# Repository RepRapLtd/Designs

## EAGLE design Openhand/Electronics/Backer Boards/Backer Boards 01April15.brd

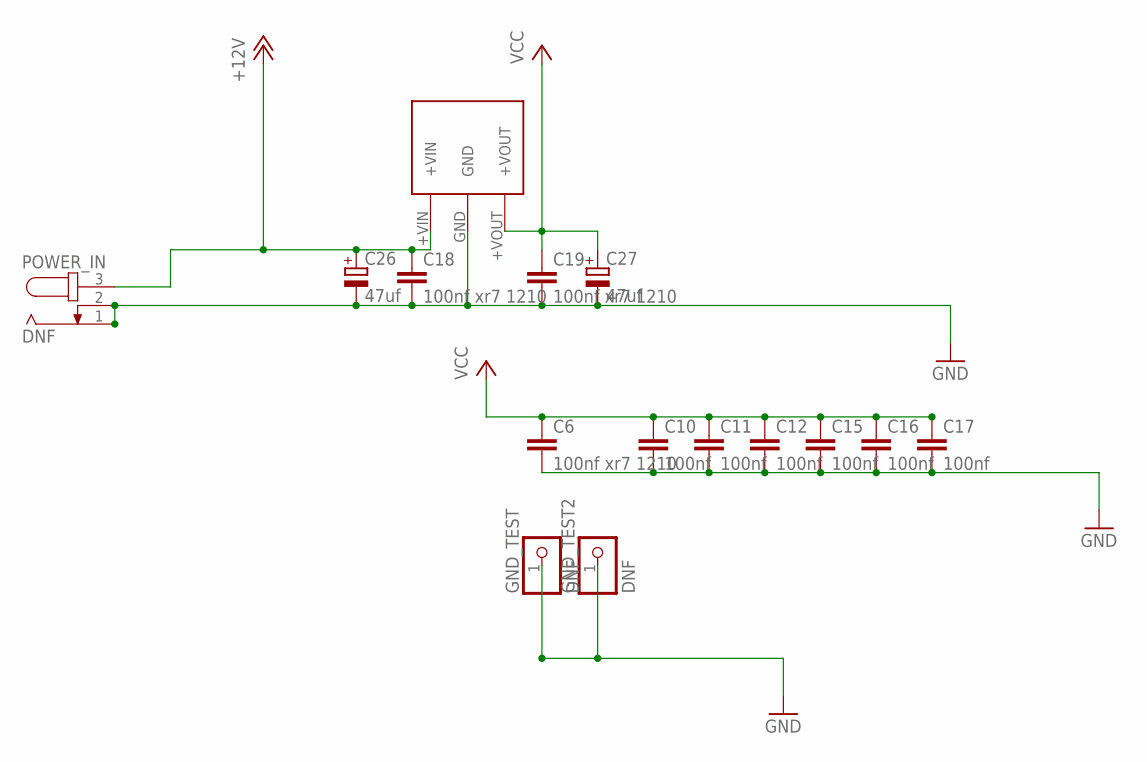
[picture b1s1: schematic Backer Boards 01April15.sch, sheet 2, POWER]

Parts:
5V_REG: DNF; 5V_RECOM_0.5A_REGULATOR
C6, C18, C19: 100nf xr7 1210; C1210
C10, C11, C12, C15, C16, C17: 100nf; C0603
C26, C27: 47uf; PANASONIC_C
GND_TEST, GND_TEST2: DNF; 1X01_ROUND
POWER_IN: DNF; SPC4078

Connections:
+12V: 5V_REG.+VIN, C18.1, C26.+, POWER_IN.3; also elsewhere on the board
GND: 5V_REG.GND, C6.2, C10.2, C11.2, C12.2, C15.2, C16.2, C17.2, C18.2, C19.2, C26.-, C27.-, GND_TEST.1, GND_TEST2.1, POWER_IN.1, POWER_IN.2; also elsewhere on the board
VCC: 5V_REG.+VOUT, C6.1, C10.1, C11.1, C12.1, C15.1, C16.1, C17.1, C19.1, C27.+; also elsewhere on the board

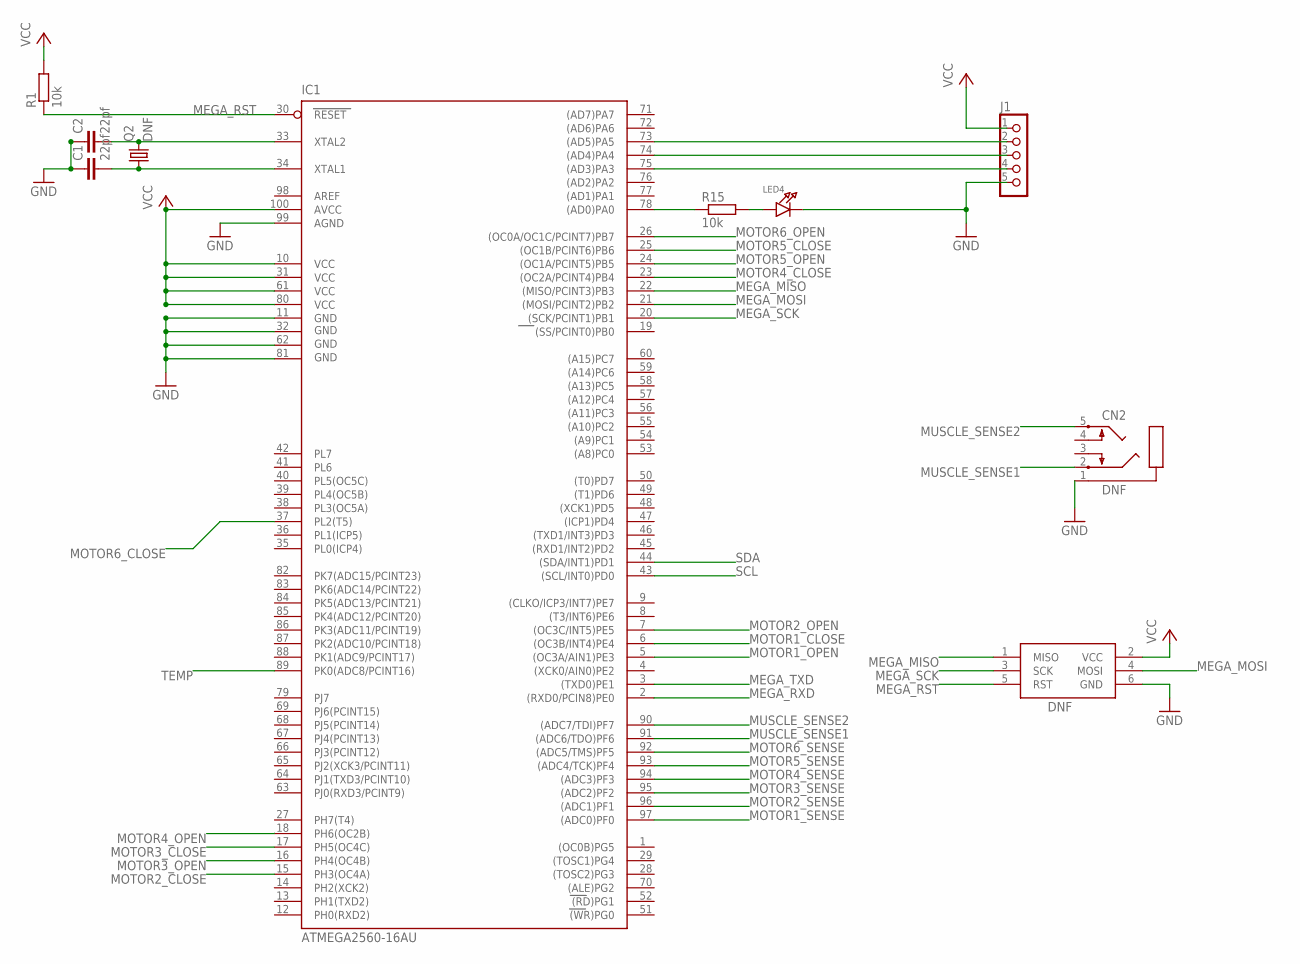
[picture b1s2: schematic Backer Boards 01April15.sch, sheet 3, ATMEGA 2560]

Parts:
C1, C2: 22pf; C0603
CN2: DNF; STX3100
DNF: AVRISP-6; AVRISP
IC1: ATMEGA2560-16AU; TQFP100
J1: DNF; M1X5
LED4: LED0805; CHIPLED_0805
Q2: DNF; HC49/S
R1, R15: 10k; R0603

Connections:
GND: C1.1, C2.1, CN2.1, DNF.6 (GND), IC1.11 (GND), IC1.32 (GND1), IC1.62 (GND2), IC1.81 (GND3), IC1.99 (AGND), J1.5, LED4.C; also elsewhere on the board
MEGA_MISO: DNF.1 (MISO), IC1.22 ((MISO/PCINT3)PB3)
MEGA_MOSI: DNF.4 (MOSI), IC1.21 ((MOSI/PCINT2)PB2)
MEGA_RST: DNF.5 (RST), IC1.30 (RESET), R1.1; also elsewhere on the board
MEGA_RXD: IC1.2 ((RXD0/PCIN8)PE0); also elsewhere on the board
MEGA_SCK: DNF.3 (SCK), IC1.20 ((SCK/PCINT1)PB1)
MEGA_TXD: IC1.3 ((TXD0)PE1); also elsewhere on the board
MOTOR1_CLOSE: IC1.6 ((OC3B/INT4)PE4); also elsewhere on the board
MOTOR1_OPEN: IC1.5 ((OC3A/AIN1)PE3); also elsewhere on the board
MOTOR1_SENSE: IC1.97 ((ADC0)PF0); also elsewhere on the board
MOTOR2_CLOSE: IC1.15 (PH3(OC4A)); also elsewhere on the board
MOTOR2_OPEN: IC1.7 ((OC3C/INT5)PE5); also elsewhere on the board
MOTOR2_SENSE: IC1.96 ((ADC1)PF1); also elsewhere on the board
MOTOR3_CLOSE: IC1.17 (PH5(OC4C)); also elsewhere on the board
MOTOR3_OPEN: IC1.16 (PH4(OC4B)); also elsewhere on the board
MOTOR3_SENSE: IC1.95 ((ADC2)PF2); also elsewhere on the board
MOTOR4_CLOSE: IC1.23 ((OC2A/PCINT4)PB4); also elsewhere on the board
MOTOR4_OPEN: IC1.18 (PH6(OC2B)); also elsewhere on the board
MOTOR4_SENSE: IC1.94 ((ADC3)PF3); also elsewhere on the board
MOTOR5_CLOSE: IC1.25 ((OC1B/PCINT6)PB6); also elsewhere on the board
MOTOR5_OPEN: IC1.24 ((OC1A/PCINT5)PB5); also elsewhere on the board
MOTOR5_SENSE: IC1.93 ((ADC4/TCK)PF4); also elsewhere on the board
MOTOR6_CLOSE: IC1.37 (PL2(T5))
MOTOR6_OPEN: IC1.26 ((OC0A/OC1C/PCINT7)PB7)
MOTOR6_SENSE: IC1.92 ((ADC5/TMS)PF5)
MUSCLE_SENSE1: CN2.2, IC1.91 ((ADC6/TDO)PF6)
MUSCLE_SENSE2: CN2.5, IC1.90 ((ADC7/TDI)PF7)
unnamed: IC1.78 ((AD0)PA0), R15.1
unnamed: LED4.A, R15.2
unnamed: IC1.75 ((AD3)PA3), J1.4
unnamed: IC1.74 ((AD4)PA4), J1.3
unnamed: IC1.73 ((AD5)PA5), J1.2
SCL: IC1.43 ((SCL/INT0)PD0)
SDA: IC1.44 ((SDA/INT1)PD1)
TEMP: IC1.89 (PK0(ADC8/PCINT16))
VCC: DNF.2 (VCC), IC1.10 (VCC), IC1.31 (VCC1), IC1.61 (VCC2), IC1.80 (VCC3), IC1.100 (AVCC), J1.1, R1.2; also elsewhere on the board
XTAL1: C1.2, IC1.34 (XTAL1), Q2.1
XTAL2: C2.2, IC1.33 (XTAL2), Q2.2

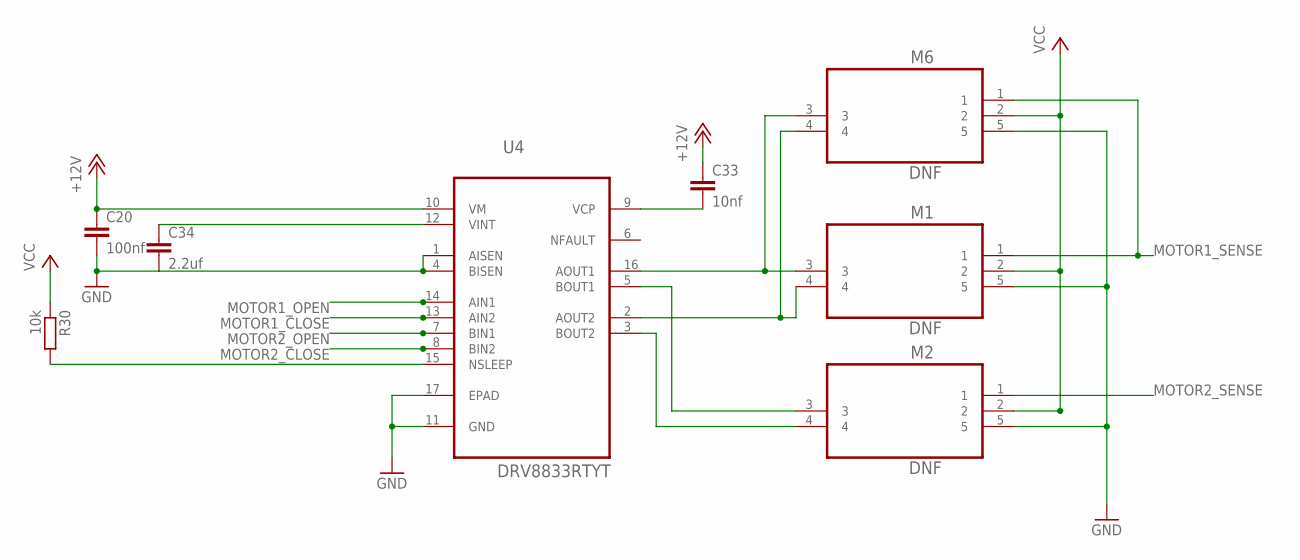
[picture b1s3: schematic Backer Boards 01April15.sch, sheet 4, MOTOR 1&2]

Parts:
C20: 100nf; C0603
C33: 10nf; C0603
C34: 2.2uf; C0603
M1, M2, M6: DNF; FCI_SFW5R-1STE1LF
R30: 10k; R0603
U4: DRV8833RTYT; QFN65P400X400X80-17N

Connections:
+12V: C20.1, C33.1, U4.10 (VM); also elsewhere on the board
GND: C20.2, C34.2, M1.5, M2.5, M6.5, U4.1 (AISEN), U4.4 (BISEN), U4.11 (GND), U4.17 (EPAD); also elsewhere on the board
MOTOR1_CLOSE: U4.13 (AIN2); also elsewhere on the board
MOTOR1_OPEN: U4.14 (AIN1); also elsewhere on the board
MOTOR1_SENSE: M1.1, M6.1; also elsewhere on the board
MOTOR2_CLOSE: U4.8 (BIN2); also elsewhere on the board
MOTOR2_OPEN: U4.7 (BIN1); also elsewhere on the board
MOTOR2_SENSE: M2.1; also elsewhere on the board
unnamed: C33.2, U4.9 (VCP)
unnamed: M1.3, M6.3, U4.16 (AOUT1)
unnamed: M1.4, M6.4, U4.2 (AOUT2)
unnamed: M2.3, U4.5 (BOUT1)
unnamed: M2.4, U4.3 (BOUT2)
unnamed: R30.2, U4.15 (NSLEEP)
unnamed: C34.1, U4.12 (VINT)
VCC: M1.2, M2.2, M6.2, R30.1; also elsewhere on the board

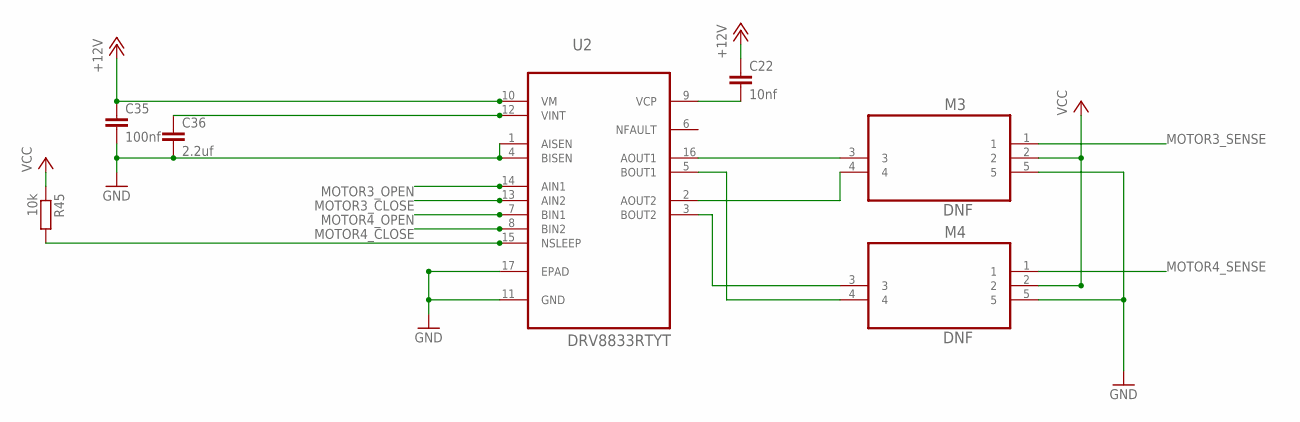
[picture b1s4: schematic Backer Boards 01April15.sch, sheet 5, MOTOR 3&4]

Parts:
C22: 10nf; C0603
C35: 100nf; C0603
C36: 2.2uf; C0603
M3, M4: DNF; FCI_SFW5R-1STE1LF
R45: 10k; R0603
U2: DRV8833RTYT; QFN65P400X400X80-17N

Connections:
+12V: C22.1, C35.1, U2.10 (VM); also elsewhere on the board
GND: C35.2, C36.2, M3.5, M4.5, U2.1 (AISEN), U2.4 (BISEN), U2.11 (GND), U2.17 (EPAD); also elsewhere on the board
MOTOR3_CLOSE: U2.13 (AIN2); also elsewhere on the board
MOTOR3_OPEN: U2.14 (AIN1); also elsewhere on the board
MOTOR3_SENSE: M3.1; also elsewhere on the board
MOTOR4_CLOSE: U2.8 (BIN2); also elsewhere on the board
MOTOR4_OPEN: U2.7 (BIN1); also elsewhere on the board
MOTOR4_SENSE: M4.1; also elsewhere on the board
unnamed: M3.3, U2.16 (AOUT1)
unnamed: M3.4, U2.2 (AOUT2)
unnamed: M4.4, U2.5 (BOUT1)
unnamed: M4.3, U2.3 (BOUT2)
unnamed: C22.2, U2.9 (VCP)
unnamed: C36.1, U2.12 (VINT)
unnamed: R45.2, U2.15 (NSLEEP)
VCC: M3.2, M4.2, R45.1; also elsewhere on the board

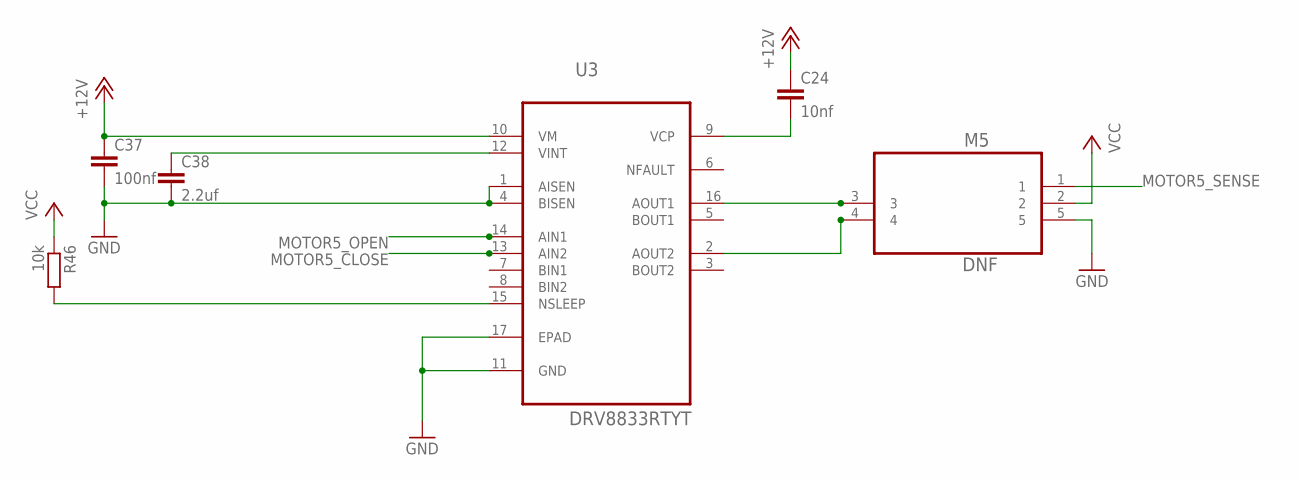
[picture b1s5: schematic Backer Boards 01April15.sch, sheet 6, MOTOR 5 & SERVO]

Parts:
C24: 10nf; C0603
C37: 100nf; C0603
C38: 2.2uf; C0603
M5: DNF; FCI_SFW5R-1STE1LF
R46: 10k; R0603
U3: DRV8833RTYT; QFN65P400X400X80-17N

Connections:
+12V: C24.1, C37.1, U3.10 (VM); also elsewhere on the board
GND: C37.2, C38.2, M5.5, U3.1 (AISEN), U3.4 (BISEN), U3.11 (GND), U3.17 (EPAD); also elsewhere on the board
MOTOR5_CLOSE: U3.13 (AIN2); also elsewhere on the board
MOTOR5_OPEN: U3.14 (AIN1); also elsewhere on the board
MOTOR5_SENSE: M5.1; also elsewhere on the board
unnamed: M5.4, U3.2 (AOUT2)
unnamed: M5.3, U3.16 (AOUT1)
unnamed: C38.1, U3.12 (VINT)
unnamed: C24.2, U3.9 (VCP)
unnamed: R46.2, U3.15 (NSLEEP)
VCC: M5.2, R46.1; also elsewhere on the board

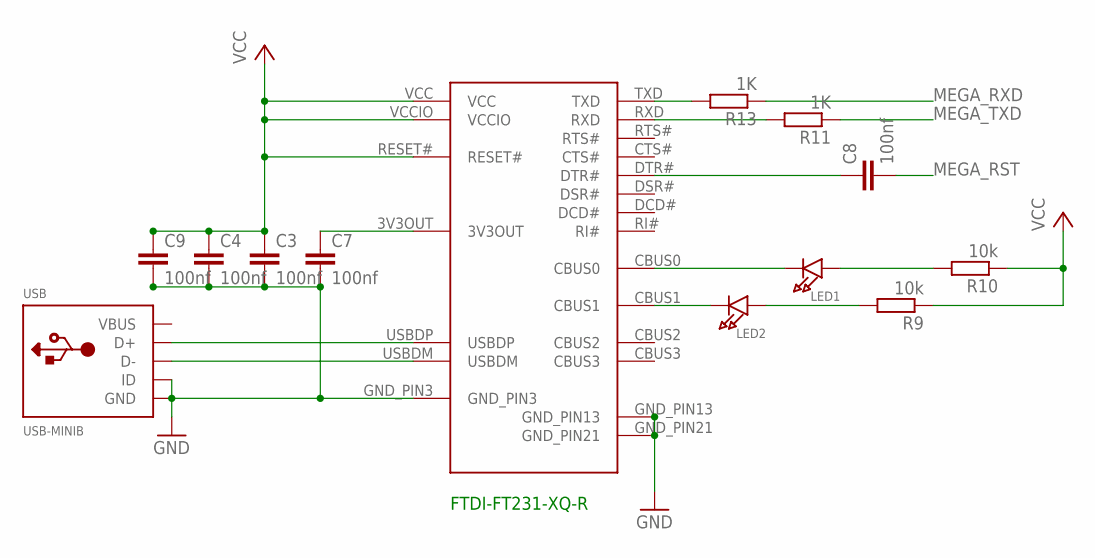
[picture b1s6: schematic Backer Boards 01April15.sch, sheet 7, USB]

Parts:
C3, C4, C7, C8, C9: 100nf; C0603
FTDI-FT231-XQ-R: FT231XQ-R; FTDI_FT231XQ-R_PACKAGE
LED1, LED2: LED0805; CHIPLED_0805
R9, R10: 10k; R0603
R11, R13: 1K; R0603
USB: USB-MINIB

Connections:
GND: C3.2, C4.2, C7.2, C9.2, FTDI-FT231-XQ-R.GND_PIN3, FTDI-FT231-XQ-R.GND_PIN13, FTDI-FT231-XQ-R.GND_PIN21, USB.GND, USB.ID; also elsewhere on the board
MEGA_RST: C8.2; also elsewhere on the board
MEGA_RXD: R13.1; also elsewhere on the board
MEGA_TXD: R11.1; also elsewhere on the board
unnamed: FTDI-FT231-XQ-R.USBDP, USB.D+
unnamed: FTDI-FT231-XQ-R.USBDM, USB.D-
unnamed: C7.1, FTDI-FT231-XQ-R.3V3OUT
unnamed: C8.1, FTDI-FT231-XQ-R.DTR#
unnamed: FTDI-FT231-XQ-R.TXD, R13.2
unnamed: FTDI-FT231-XQ-R.RXD, R11.2
unnamed: FTDI-FT231-XQ-R.CBUS0, LED1.C
unnamed: FTDI-FT231-XQ-R.CBUS1, LED2.C
unnamed: LED2.A, R9.2
unnamed: LED1.A, R10.2
VBUS: USB.VBUS
VCC: C3.1, C4.1, C9.1, FTDI-FT231-XQ-R.RESET#, FTDI-FT231-XQ-R.VCC, FTDI-FT231-XQ-R.VCCIO, R9.1, R10.1; also elsewhere on the board

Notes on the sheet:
FTDI-FT231-XQ-R

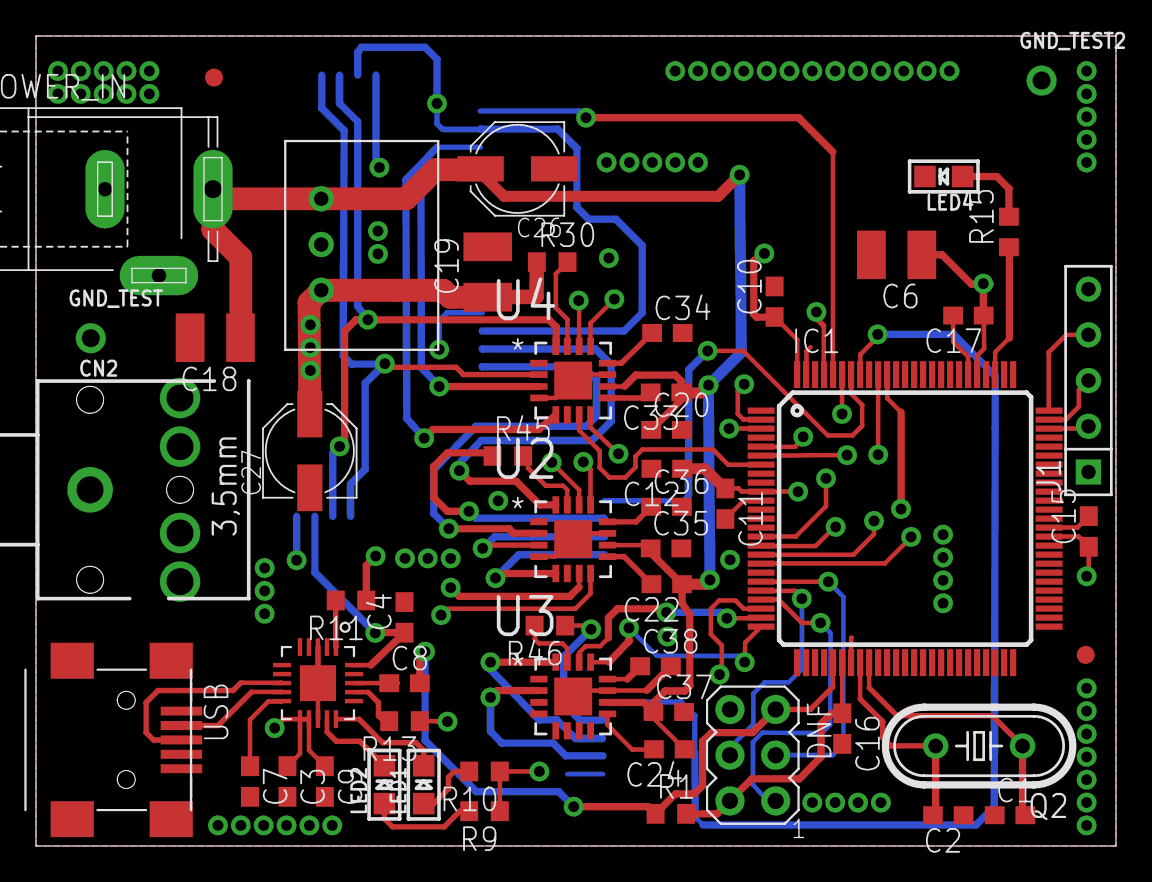
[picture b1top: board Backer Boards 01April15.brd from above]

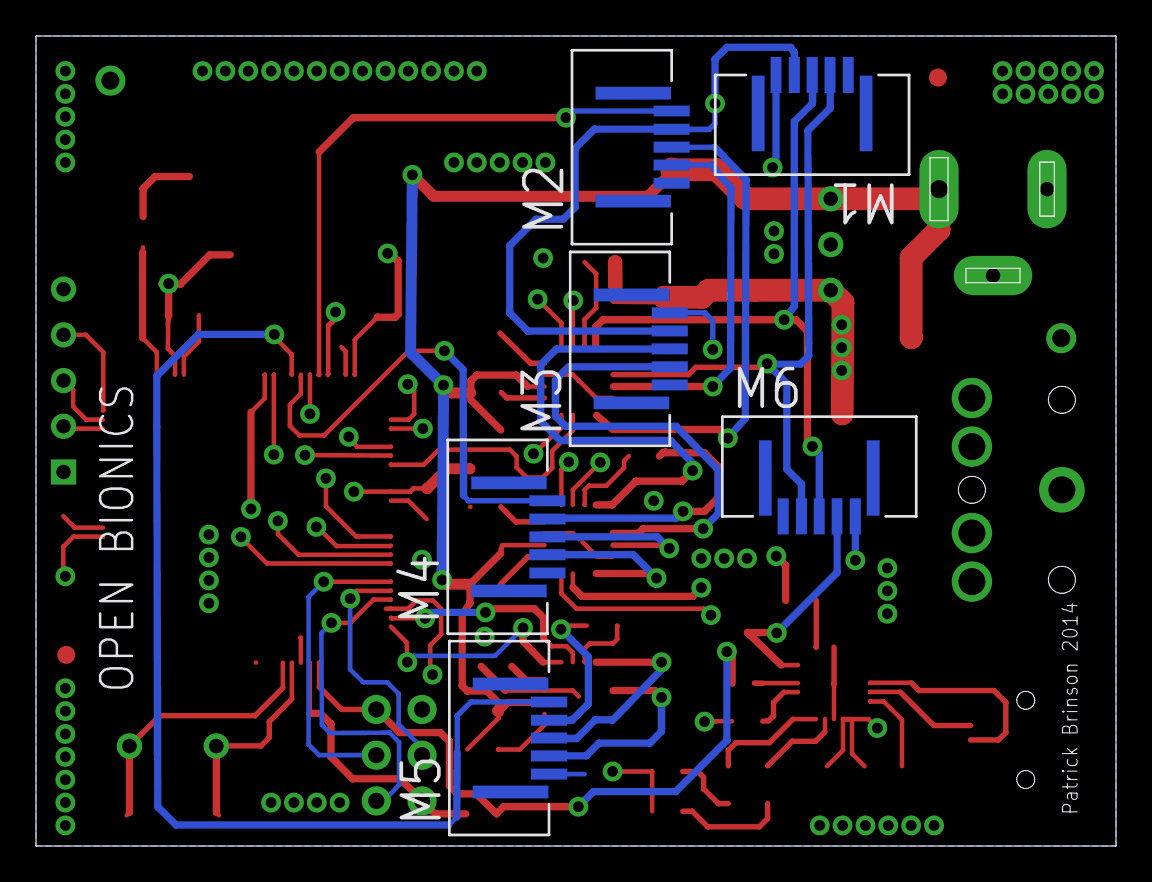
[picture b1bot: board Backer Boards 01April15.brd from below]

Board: 4 copper layers, 60.0 x 45.0 mm, 61 parts (6 on the bottom side), 62 nets.

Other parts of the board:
U$1, U$2: FIDUCIAL_G10

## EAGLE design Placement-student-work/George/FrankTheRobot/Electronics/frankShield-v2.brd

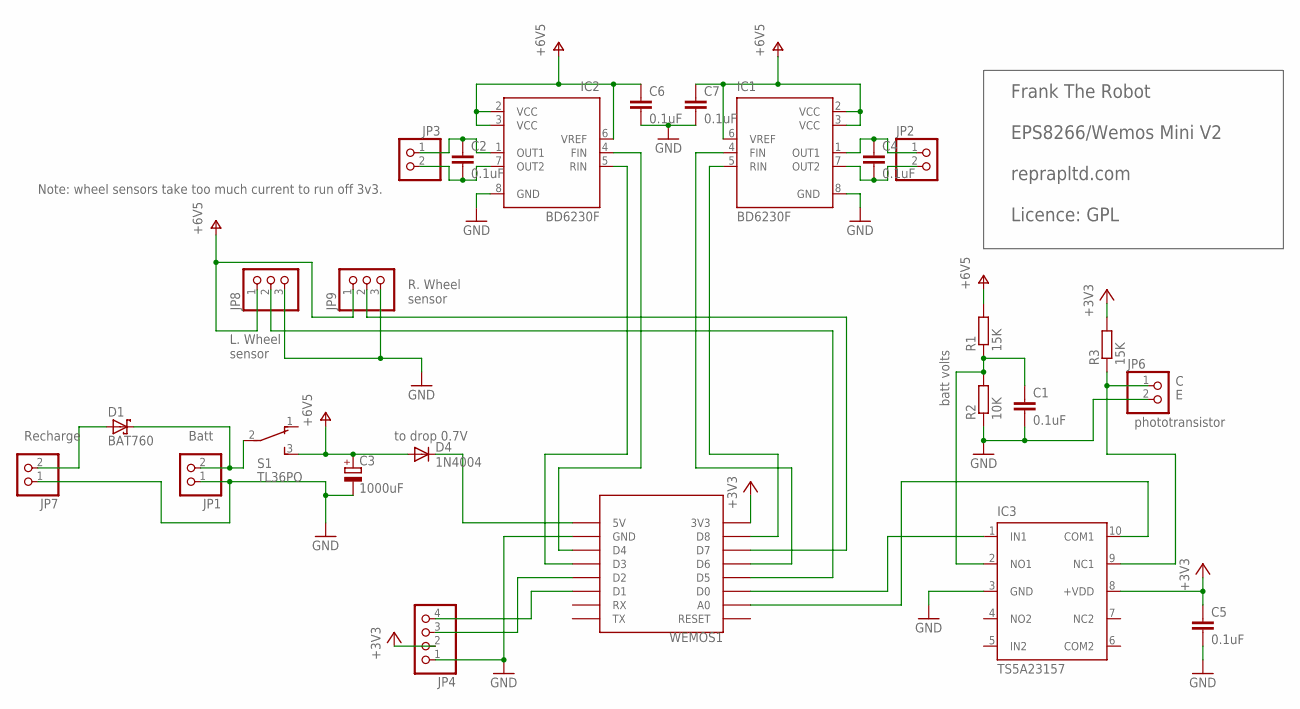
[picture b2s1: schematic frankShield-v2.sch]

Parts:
C1, C2, C4, C5, C6, C7: 0.1uF; C0805
C3: 1000uF; B45181B
D1: BAT760; SOD323_ST
D4: 1N4004; DO41-10
IC1, IC2: BD6230F; SOP8
IC3: TS5A23157; MSOP10
JP1, JP2, JP3, JP6, JP7: PINHD-1X2; 1X02
JP4: PINHD-1X4; 1X04
JP8, JP9: PINHD-1X3; 1X03
R1, R3: 15K; M0805
R2: 10K; M0805
S1: TL36PO; TL3XPO
WEMOS1: WEMOS-D1-MINI

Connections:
+3V3: C5.1, IC3.8 (+VDD), JP4.2, R3.2, WEMOS1.3V3
GND: C1.2, C3.-, C5.2, C6.2, C7.2, IC1.8 (GND), IC2.8 (GND), IC3.3 (GND), JP1.1, JP4.1, JP6.2, JP7.1, JP8.3, JP9.3, R2.1, WEMOS1.GND
unnamed: JP4.4, WEMOS1.D1
unnamed: JP4.3, WEMOS1.D2
unnamed: C2.1, IC2.1 (OUT1), JP3.1
unnamed: C2.2, IC2.7 (OUT2), JP3.2
unnamed: C4.1, IC1.1 (OUT1), JP2.1
unnamed: C4.2, IC1.7 (OUT2), JP2.2
unnamed: IC2.4 (FIN), WEMOS1.D4
unnamed: IC2.5 (RIN), WEMOS1.D3
unnamed: IC1.4 (FIN), WEMOS1.D6
unnamed: IC1.5 (RIN), WEMOS1.D8
unnamed: IC3.10 (COM1), WEMOS1.A0
unnamed: C1.1, IC3.2 (NO1), R1.1, R2.2
unnamed: D1.C, JP1.2, S1.2
unnamed: IC3.9 (NC1), JP6.1, R3.1
unnamed: IC3.1 (IN1), WEMOS1.D0
unnamed: D1.A, JP7.2
unnamed: JP9.2, WEMOS1.D7
unnamed: JP8.2, WEMOS1.D5
unnamed: D4.C, WEMOS1.5V
NC2: IC3.7 (NC2)
V+: C3.+, C6.1, C7.1, D4.A, IC1.2 (VCC), IC1.3 (VCC), IC1.6 (VREF), IC2.2 (VCC), IC2.3 (VCC), IC2.6 (VREF), JP8.1, JP9.1, R1.2, S1.3 (S)

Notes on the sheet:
phototransistor
Frank The Robot EPS8266/Wemos Mini V2 reprapltd.com Licence: GPL
Batt
Recharge
L. Wheel sensor
R. Wheel sensor
batt volts
Note: wheel sensors take too much current to run off 3v3.
to drop 0.7V

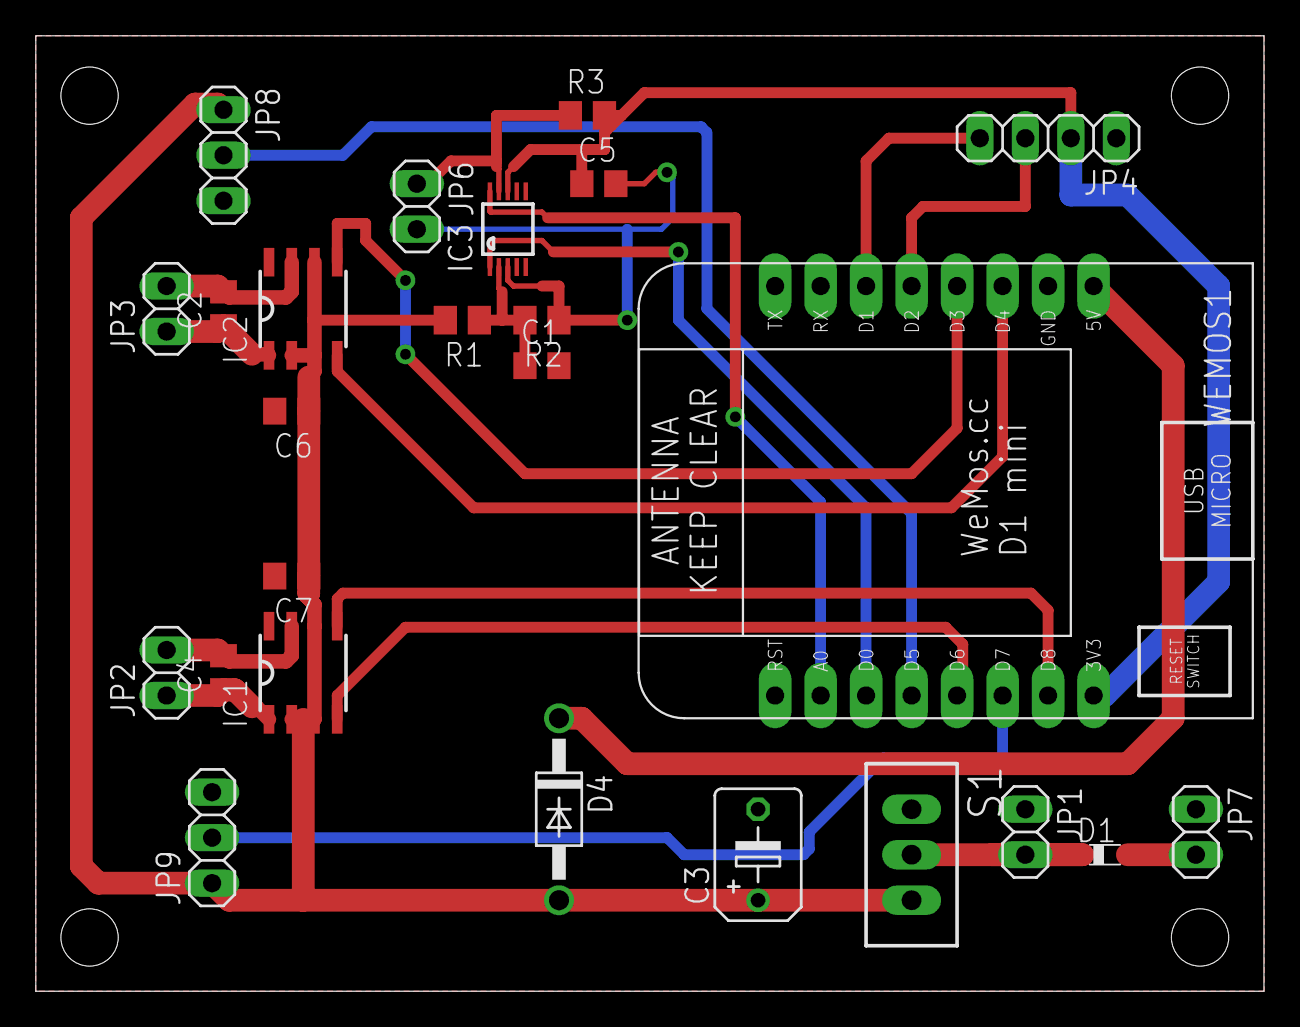
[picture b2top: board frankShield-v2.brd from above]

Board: 2 copper layers, 68.6 x 53.3 mm, 25 parts (0 on the bottom side), 22 nets.

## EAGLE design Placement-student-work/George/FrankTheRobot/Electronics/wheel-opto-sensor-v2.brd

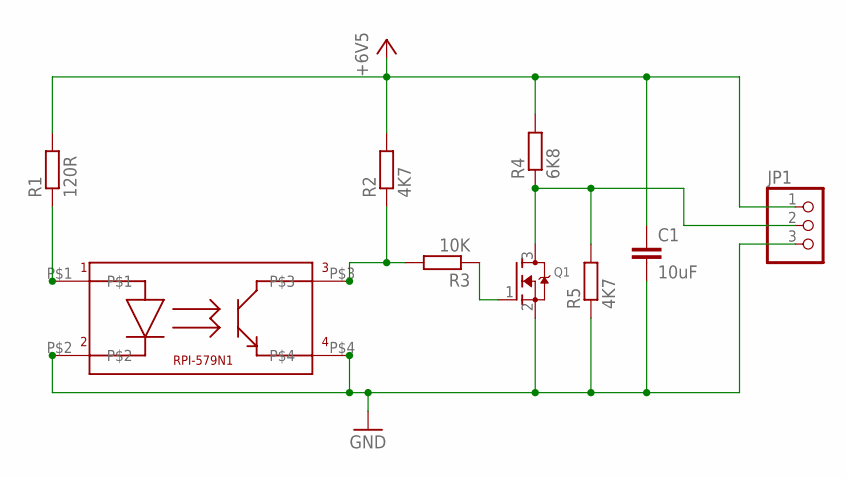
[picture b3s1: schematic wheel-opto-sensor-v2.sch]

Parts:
C1: 10uF; C1206
JP1: PINHD-1X3; 1X03
Q1: MOSFET-NREFLOW; SOT23
R1: 120R; M0805
R2, R5: 4K7; M0805
R3: 10K; M0805
R4: 6K8; M0805
U$1: RPI-579N1

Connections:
+6V5: C1.1, JP1.1, R1.2, R2.2, R4.2
GND: C1.2, JP1.3, Q1.2 (S), R5.1, U$1.P$2, U$1.P$4
unnamed: JP1.2, Q1.3 (D), R4.1, R5.2
unnamed: R1.1, U$1.P$1
unnamed: Q1.1 (G), R3.1
unnamed: R2.1, R3.2, U$1.P$3

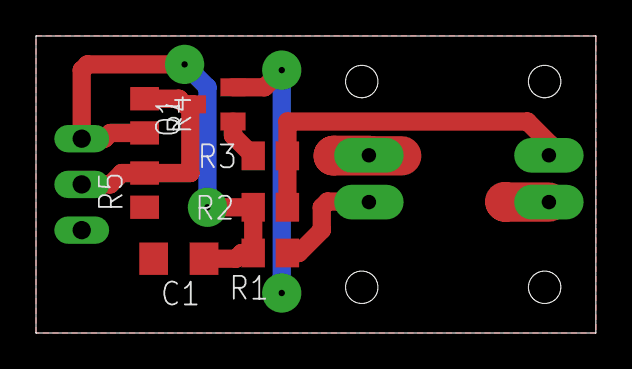
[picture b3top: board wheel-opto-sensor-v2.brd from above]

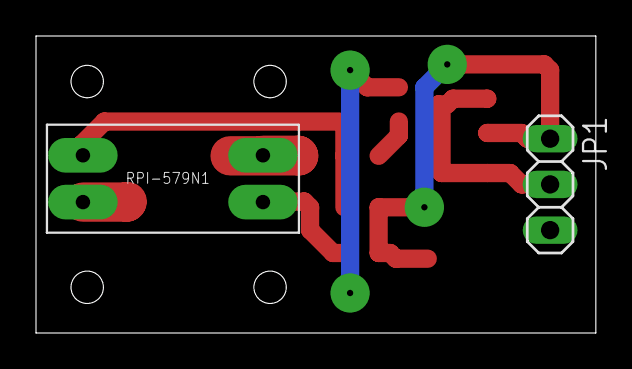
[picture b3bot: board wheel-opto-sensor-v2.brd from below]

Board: 2 copper layers, 31.1 x 16.5 mm, 9 parts (2 on the bottom side), 6 nets.

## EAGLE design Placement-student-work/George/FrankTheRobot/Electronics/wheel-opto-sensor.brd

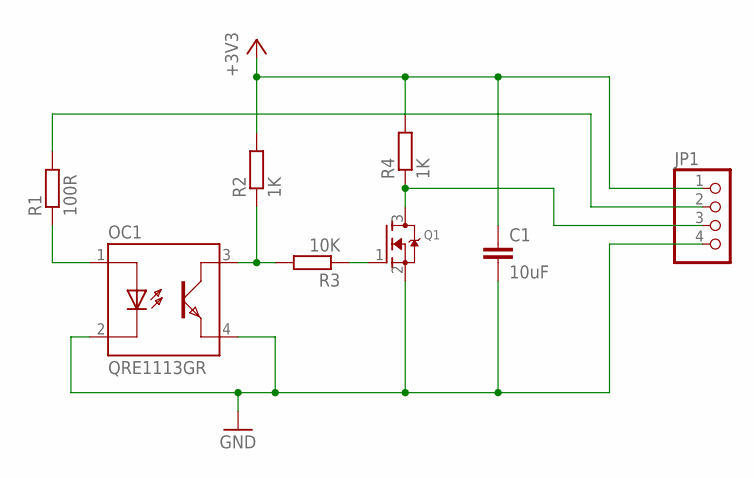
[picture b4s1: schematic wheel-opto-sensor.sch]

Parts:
C1: 10uF; C1206
JP1: PINHD-1X4; 1X04
OC1: QRE1113GR; SMT_GULLWING_4
Q1: MOSFET-NREFLOW; SOT23
R1: 100R; M0805
R2, R4: 1K; M0805
R3: 10K; M0805

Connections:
+3V3: C1.1, JP1.1, R2.2, R4.2
GND: C1.2, JP1.4, OC1.2 (C), OC1.4 (TE), Q1.2 (S)
unnamed: JP1.3, Q1.3 (D), R4.1
unnamed: OC1.1 (A), R1.1
unnamed: JP1.2, R1.2
unnamed: Q1.1 (G), R3.1
unnamed: OC1.3 (TC), R2.1, R3.2

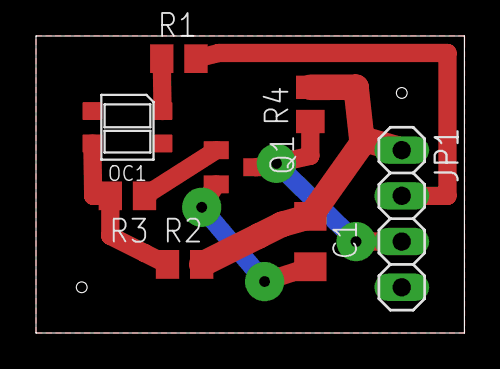
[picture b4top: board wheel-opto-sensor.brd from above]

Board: 2 copper layers, 23.8 x 16.5 mm, 8 parts (0 on the bottom side), 7 nets.

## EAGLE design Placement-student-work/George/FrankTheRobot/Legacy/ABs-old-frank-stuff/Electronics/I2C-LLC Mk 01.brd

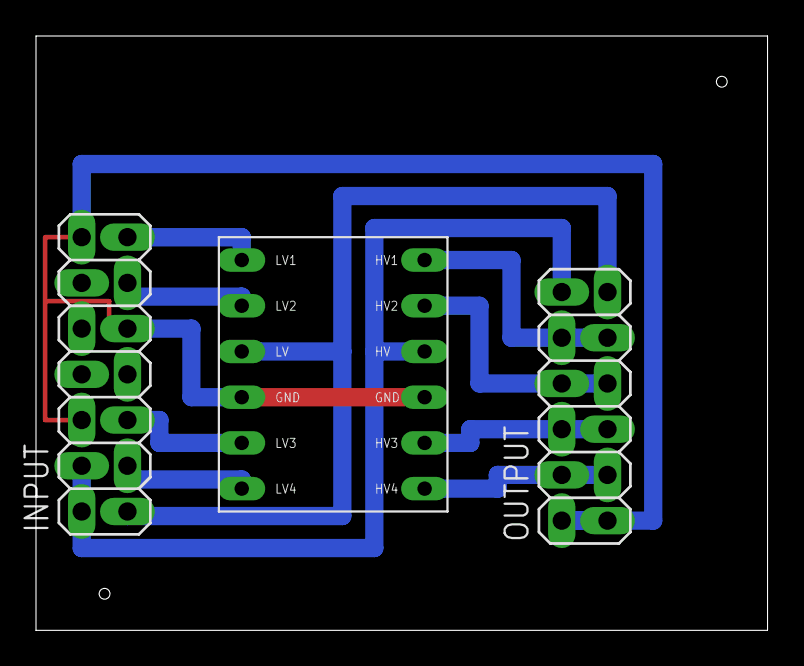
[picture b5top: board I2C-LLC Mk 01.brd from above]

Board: 2 copper layers, 40.6 x 33.0 mm, 3 parts (0 on the bottom side), 11 nets.

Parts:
INPUT: 2X07
OUTPUT: 2X06
U$1: BD-LLC

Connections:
+3V3: INPUT.1, OUTPUT.11, U$1.LV_IN
+5V: INPUT.2, INPUT.4, OUTPUT.12, U$1.HV_IN
EX1_H: OUTPUT.7, OUTPUT.8, U$1.HV2
EX1_L: INPUT.11, U$1.LV2
EX2_H: OUTPUT.9, OUTPUT.10, U$1.HV1
EX2_L: INPUT.13, U$1.LV1
GND: INPUT.6, INPUT.9, INPUT.14, OUTPUT.1, OUTPUT.2, U$1.GND1, U$1.GND2
SCK_H: OUTPUT.5, OUTPUT.6, U$1.HV3
SCK_L: INPUT.5, U$1.LV3
SDA_H: OUTPUT.3, OUTPUT.4, U$1.HV4
SDA_L: INPUT.3, U$1.LV4

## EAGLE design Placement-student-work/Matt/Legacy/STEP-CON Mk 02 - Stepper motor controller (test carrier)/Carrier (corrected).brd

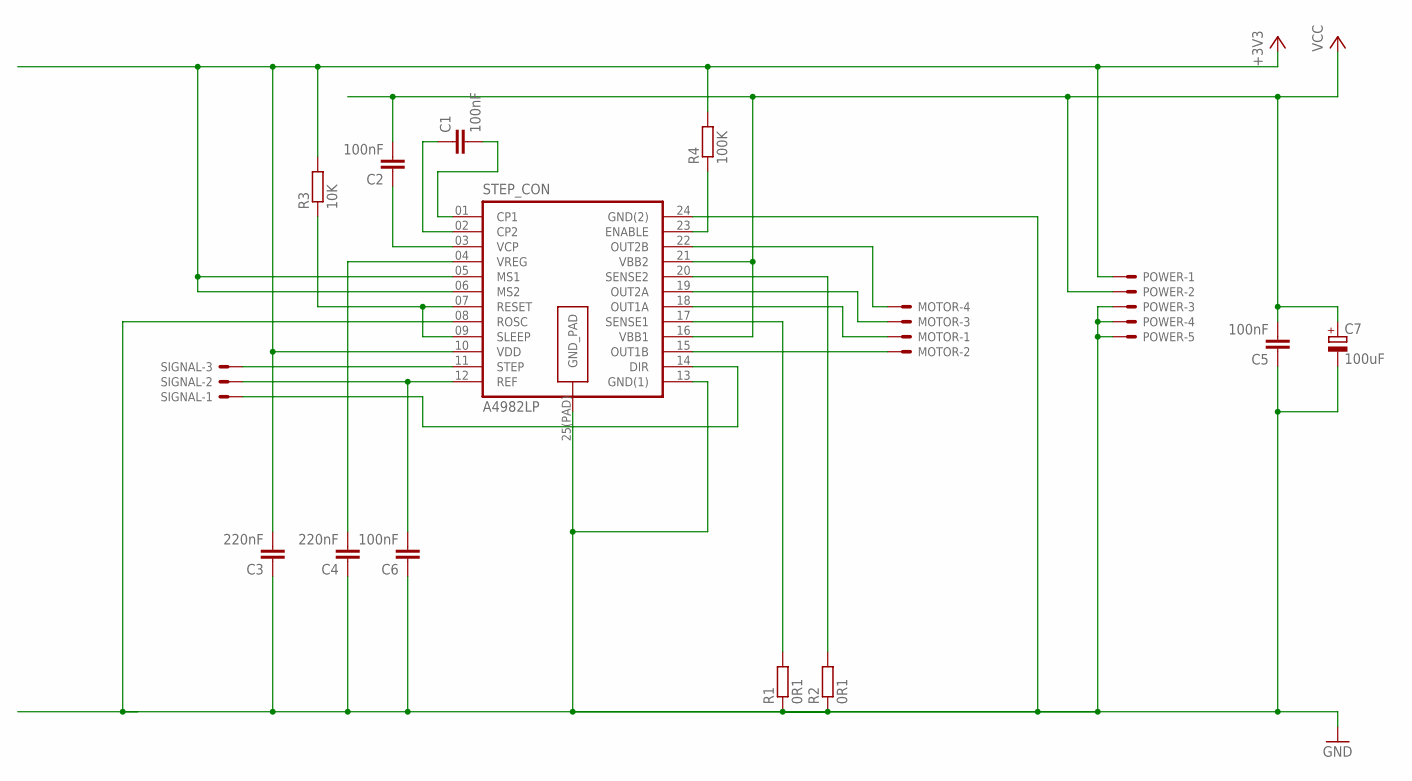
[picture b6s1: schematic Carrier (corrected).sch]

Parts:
C1, C2, C5, C6: 100nF; C1206
C3, C4: 220nF; C1206
C7: 100uF; B45181A
MOTOR: KK-156-4
POWER: KK-156-5
R1, R2: 0R1; M0805
R3: 10K; M0805
R4: 100K; M0805
SIGNAL: KK-156-3
STEP_CON: A4982LP

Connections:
+3V3: C3.2, POWER.1, R3.2, R4.2, STEP_CON.05 (MS1), STEP_CON.06 (MS2), STEP_CON.10 (VDD)
CP1: C1.2, STEP_CON.01 (CP1)
CP2: C1.1, STEP_CON.02 (CP2)
DIR: SIGNAL.1, STEP_CON.14 (DIR)
ENABLE: R4.1, STEP_CON.23 (ENABLE)
GND: C3.1, C4.1, C5.1, C6.1, C7.-, POWER.3, POWER.4, POWER.5, R1.1, R2.1, STEP_CON.08 (ROSC), STEP_CON.13 (GND(1)), STEP_CON.24 (GND(2)), STEP_CON.25(PAD) (GND_PAD)
OUT1A: MOTOR.1, STEP_CON.18 (OUT1A)
OUT1B: MOTOR.2, STEP_CON.15 (OUT1B)
OUT2: MOTOR.3, STEP_CON.19 (OUT2A)
OUT2B: MOTOR.4, STEP_CON.22 (OUT2B)
REF: C6.2, SIGNAL.2, STEP_CON.12 (REF)
RESET+SLEEP: R3.1, STEP_CON.07 (RESET), STEP_CON.09 (SLEEP)
SENSE: R2.2, STEP_CON.20 (SENSE2)
SENSE1: R1.2, STEP_CON.17 (SENSE1)
STEP: SIGNAL.3, STEP_CON.11 (STEP)
VCC: C2.2, C5.2, C7.+, POWER.2, STEP_CON.16 (VBB1), STEP_CON.21 (VBB2)
VCP: C2.1, STEP_CON.03 (VCP)
VREG: C4.2, STEP_CON.04 (VREG)

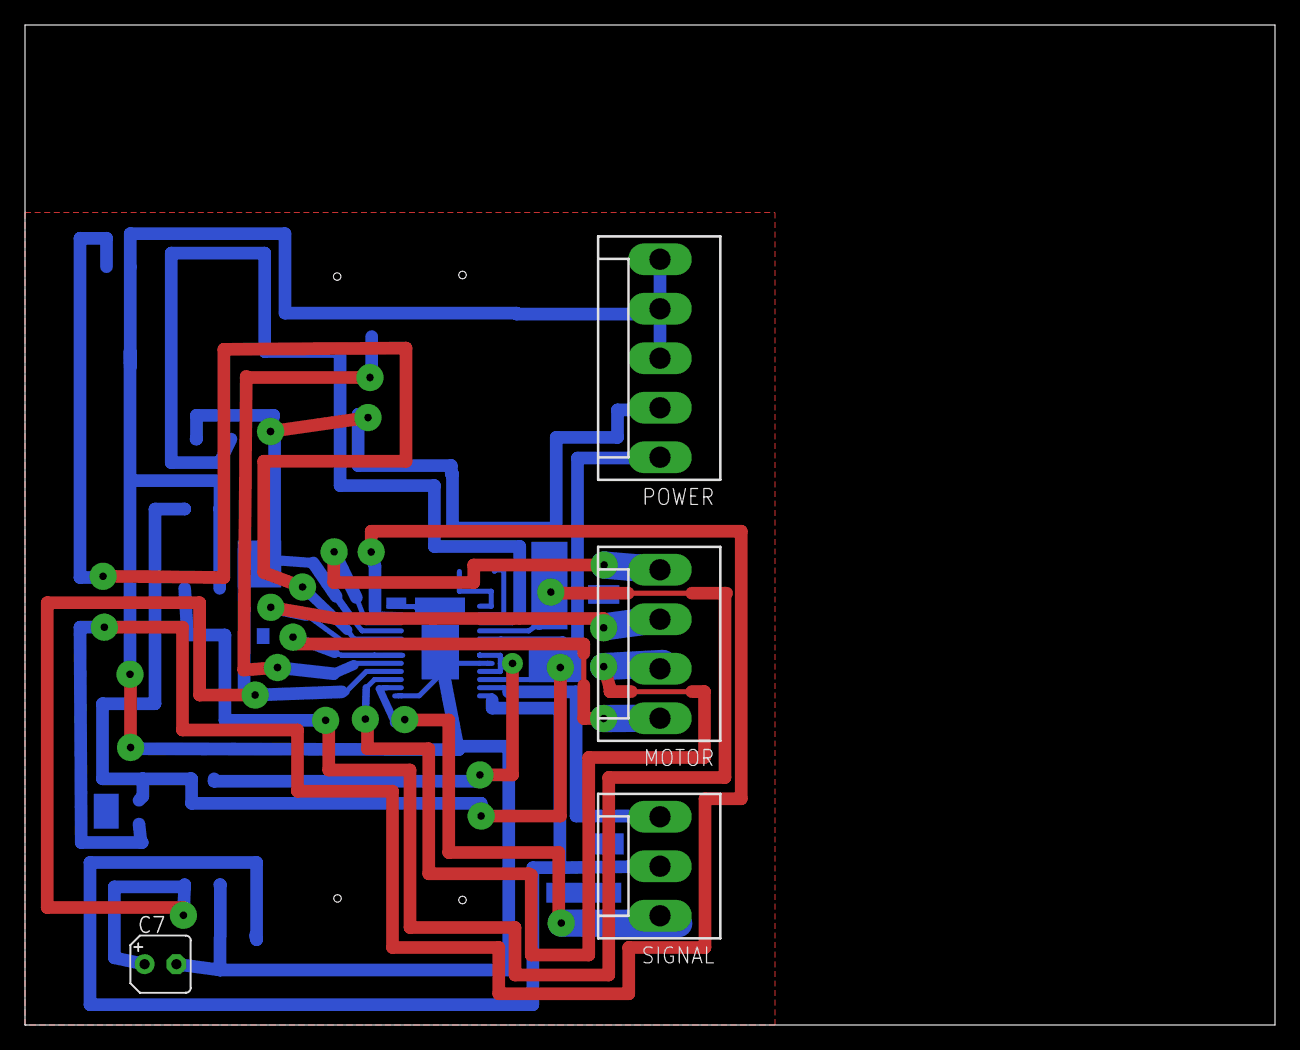
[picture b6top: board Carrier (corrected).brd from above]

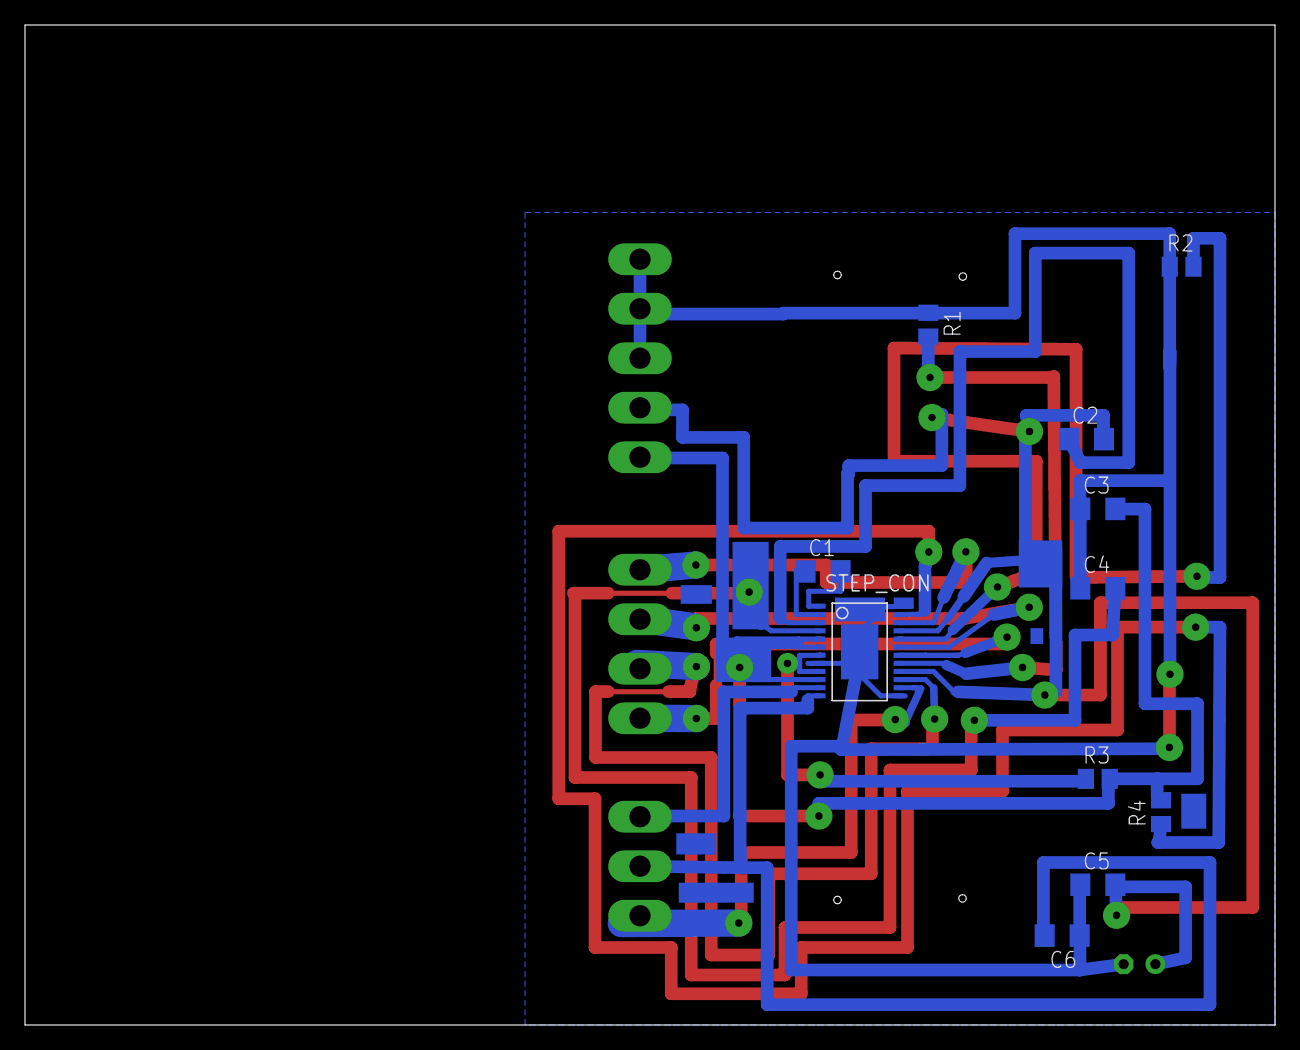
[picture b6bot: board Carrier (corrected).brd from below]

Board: 2 copper layers, 100.0 x 80.0 mm, 15 parts (11 on the bottom side), 18 nets.

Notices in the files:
parts and their libraries:
microbuilder: This work is placed in the public domain, and may be freely used for commercial and non-commercial work with the following conditions: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
dicons: Copyright (C) 2004, Bob Starr (rtzaudio@mindspring.com)
